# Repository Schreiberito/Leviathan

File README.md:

# Leviathan- Aquarium Automation Circuit Board for Reef-Pi
### [Link to Leviathan's Website](https://sites.google.com/view/leviathan-aquarium/home)
The Leviathan board pairs with a Raspberry Pi running the free, open-source Reef-Pi software. This combination allows the simple & affordable automation of virtually any aquarium.

## Features:
* Equipment Control- 12 GPIO Output for Equipment Relay control
* Dosing Control- 4 variable voltage outputs for 2 dosing pumps
* Lighting Control- 8 PWM outputs for Spectrum & Intensity control for 4 Lights
* pH Monitoring- i2C connection for pH probe
* Temperature Monitoring- 3 inputs for DS18B20 temperature probes
* Auto Top-Off Control-2 optical sensor inputs & 2 mechanical float switch inputs

(Click the board image below for a video demonstration of the board's use)

## DC Power Inputs:
* 12V for powering buck converters & L293D
* 10V for 10V PWM light control logic
* 5V for Raspberry Pi, Optical Sensors, PCA9685, & L293D

## Schematic

## Internal PCB Routing

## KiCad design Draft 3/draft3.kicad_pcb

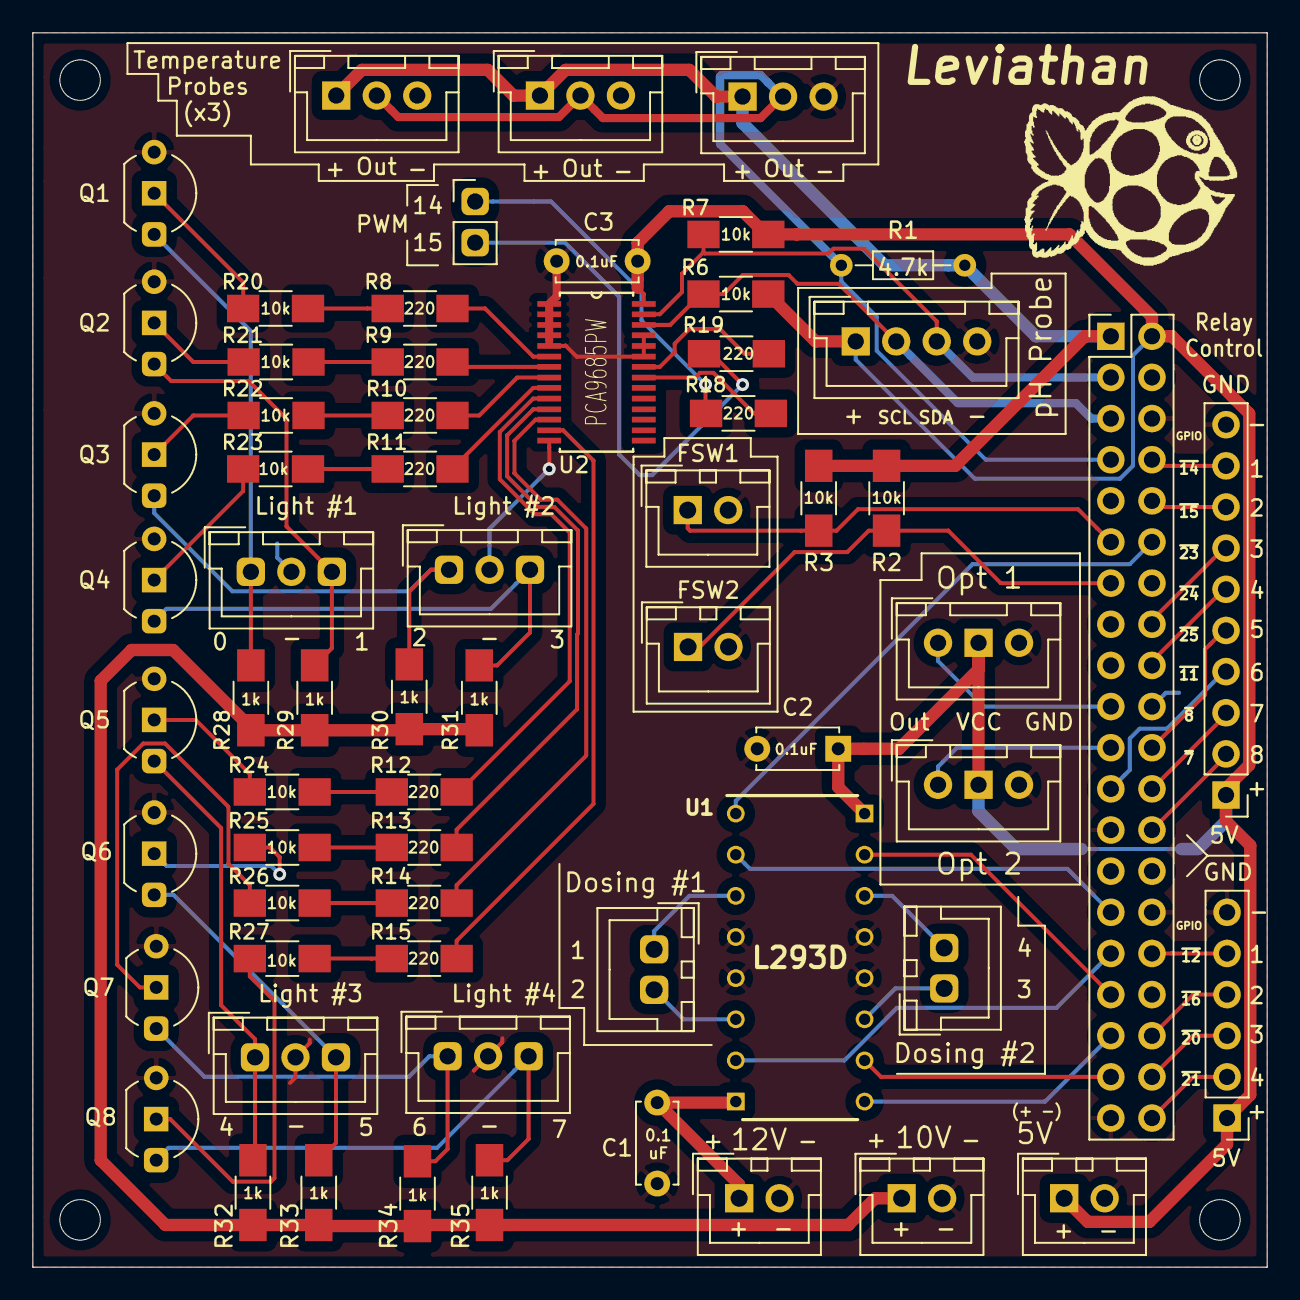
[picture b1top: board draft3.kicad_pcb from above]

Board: 2 copper layers, 76.2 x 76.2 mm, 70 parts (0 on the bottom side), 70 nets.

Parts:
C1, C2, C3: 0.1uF; C_Disc_D5.0mm_W2.5mm_P5.00mm
FSW1: Float Switch 1; JST_XH_B02B-XH-A_02x2.50mm_Straight
FSW2: Float Switch 2; JST_XH_B02B-XH-A_02x2.50mm_Straight
H1, H2, H3, H4: MountingHole_Pad; MountingHole_2.5mm
H5: Logo(Small); Logo
J1: Dose Motor 1 Conn.; JST_XH_B02B-XH-A_02x2.50mm_Straight
J2: Dose Motor 2 Conn.; JST_XH_B02B-XH-A_02x2.50mm_Straight
J3, J4, J5: 3.5mm Jack; JST_XH_B03B-XH-A_03x2.50mm_Straight(Audio)
J6: pH Connector; JST_XH_B04B-XH-A_04x2.50mm_Straight
J7: 8 Relay Conn.; Pin_Header_Straight_1x10_Pitch2.54mm
J8: 4 Relay Conn.; Pin_Header_Straight_1x06_Pitch2.54mm
J9: Opt 1; JST_XH_B03B-XH-A_03x2.50mm_Straight
J10: Opt 2; JST_XH_B03B-XH-A_03x2.50mm_Straight
J11: PWM14&15; Pin_Header_Straight_1x02_Pitch2.54mm
J12: Raspberry Pi Pins; Pin_Header_Straight_2x20_Pitch2.54mm
J13: 12V In; JST_XH_B02B-XH-A_02x2.50mm_Straight
J14: 5V In; JST_XH_B02B-XH-A_02x2.50mm_Straight
J15: 10V In; JST_XH_B02B-XH-A_02x2.50mm_Straight
J16: Light1; JST_XH_B03B-XH-A_03x2.50mm_Straight
J17: Light2; JST_XH_B03B-XH-A_03x2.50mm_Straight
J18: Light3; JST_XH_B03B-XH-A_03x2.50mm_Straight
J19: Light4; JST_XH_B03B-XH-A_03x2.50mm_Straight
Q1, Q2, Q3, Q4, Q5, Q6, Q7, Q8: NPN; TO-92_Inline_Wide
R1: 4.7k; R_Axial_DIN0204_L3.6mm_D1.6mm_P7.62mm_Horizontal
R2, R3, R6, R7, R20, R21, R22, R23, R24, R25, R26, R27: 10k; R_1206_HandSoldering
R8, R9, R10, R11, R12, R13, R14, R15, R18, R19: 220; R_1206_HandSoldering
R28, R29, R30, R31, R32, R33, R34, R35: 1k; R_1206_HandSoldering
U1: L293D; DIP795W50P254L2000H510Q16N
U2: PCA9685PW; SOP65P640X110-28N

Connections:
3.3V: J3.T, J4.T, J5.T, J12.1, R1.1, R2.1, R3.1
5V: C2.2, C3.1, J6.1, J7.1, J8.1, J9.2, J10.2, J12.2, J14.1, R6.1, R7.1, U1.16, U2.28
10V: J15.1, R28.1, R29.1, R30.1, R31.1, R32.1, R33.1, R34.1, R35.1
12V: C1.1, J13.1, U1.8
GND: C1.2, C2.1, C3.2, FSW1.2, FSW2.2, J3.G, J4.G, J5.G, J6.4, J7.10, J8.6, J9.3, J10.3, J12.6, J12.9, J12.14, J12.20, J12.25, J12.30, J12.34, J12.39, J13.2, J14.2, J15.2, J16.2, J17.2, J18.2, J19.2, Q1.1, Q2.1, Q3.1, Q4.1, Q5.1, Q6.1, Q7.1, Q8.1, U1.4, U1.5, U1.12, U1.13, U2.1, U2.2, U2.3, U2.4, U2.5, U2.14, U2.23, U2.24, U2.25
unnamed: J1.1, U1.3
unnamed: J1.2, U1.6
unnamed: J2.1, U1.11
unnamed: J2.2, U1.14
unnamed: J16.1, Q1.3, R28.2
unnamed: J16.3, Q2.3, R29.2
unnamed: J17.1, Q3.3, R30.2
unnamed: J17.3, Q4.3, R31.2
unnamed: J18.1, Q5.3, R32.2
unnamed: J18.3, Q6.3, R33.2
unnamed: J19.1, Q7.3, R34.2
unnamed: J19.3, Q8.3, R35.2
unnamed: Q1.2, R20.1
unnamed: Q2.2, R21.1
unnamed: Q3.2, R22.1
unnamed: Q4.2, R23.1
unnamed: Q5.2, R24.1
unnamed: Q6.2, R25.1
unnamed: Q7.2, R26.1
unnamed: Q8.2, R27.1
unnamed: R8.2, U2.6
unnamed: R9.2, U2.7
unnamed: R10.1, R22.2
unnamed: R10.2, U2.8
unnamed: R11.1, R23.2
unnamed: R11.2, U2.9
unnamed: R12.1, R24.2
unnamed: R12.2, U2.10
unnamed: R13.1, R25.2
unnamed: R13.2, U2.11
unnamed: R14.1, R26.2
unnamed: R14.2, U2.12
unnamed: R15.1, R27.2
unnamed: R15.2, U2.13
unnamed: R18.2, U2.21
unnamed: R19.2, U2.22
unnamed: R8.1, R20.2
unnamed: R9.1, R21.2
PWM14: J11.1, R18.1
PWM15: J11.2, R19.1
SCL: J6.2, J12.5, R6.2, U2.26
SDA: J6.3, J12.3, R7.2, U2.27
~4: J3.S, J4.S, J5.S, J12.7, R1.2
~5: J12.29, U1.2
~6: J12.31, U1.7
~7: J7.2, J12.26
~8: J7.3, J12.24
~9: J10.1, J12.21
~10: J9.1, J12.19
~11: J7.4, J12.23
~12: J8.5, J12.32
~13: J12.33, U1.15
~14: J7.9, J12.8
~15: J7.8, J12.10
~16: J8.4, J12.36
~17: FSW1.1, J12.11, R3.2
~18: J12.12, U1.1
~19: J12.35, U1.9
~20: J8.3, J12.38
~21: J8.2, J12.40
~23: J7.7, J12.16
~24: J7.6, J12.18
~25: J7.5, J12.22
~26: J12.37, U1.10
~27: FSW2.1, J12.13, R2.2

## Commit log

2020-01-03 Licensed under the TAPR Open Hardware License (www.tapr.org/OHL)
    Layman's explanation of the license:
    -You may modify the documentation and make products based upon it.
    -You may use products for any legal purpose without limitation.
    -You may distribute unmodified documentation, but you must include the complete package as you received it.
    -You may distribute products you make to third parties, if you either include the documentation on which the product is based, or make it available without charge for at least three years to anyone w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
    You may distribute modified documentation or products based on it, if you:
2020-01-03 Contributor List
    Add your name & email if you contribute to Leviathan & wish to be notified of changes to the design
2020-01-03 Deleted License.txt
    Fixing formatting
2020-01-03 Licensed under the TAPR Open Hardware License (www.tapr.org/OHL)
    ***Layman's explanation of the license, full license at www.tapr.org/OHL***
    -You may modify the documentation and make products based upon it.
    -You may use products for any legal purpose without limitation.
    -You may distribute unmodified documentation, but you must include the complete package as you received it.
    -You may distribute products you make to third parties, if you either include the documentation on which the product is based, or make it available without charge for at least three years to anyone w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
    You may distribute modified documentation or products based on it, if you:
2020-01-03 Create Draft 3 folder
2020-01-03 Gerber Files
2020-01-03 Added KiCad project
    This file contains the KiCad project which houses the schematic & board layout.
2020-01-03 Delete draft3.pro
    Needs support files to work. Will just upload .sch & .kicad_pcb files.
2020-01-03 Added PCB file
2020-01-03 Added schematic file
2020-01-03 Create Images README
2020-01-03 Added image of populated Leviathan board
2020-01-03 Added image of unpopulated board
2020-01-03 Adding image of unpopulated board
2020-01-03 Deleting image that was too large
    Initial upload was 6,000 x 4,000 pixels.
2020-01-03 Added unpopulated board image
2020-01-03 Added smaller unpopulated board picture
2020-01-03 Testing youtube video link
2020-01-03 Added features & Power Inputs
2020-01-03 Added Title Block info
2020-01-03 Re-added schematic with correct PCA9685pw address
2020-01-03 Added schematic image
2020-01-03 Added image of PCB routing
2020-01-03 Added Documentation Draft
    This documentation is still very much a work in progress. It has not been edited for correctness, grammar, formatting, etc. Treat it as a rough reference for now, refer to the Adafruit guide for any 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
